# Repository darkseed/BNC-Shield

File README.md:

Documentation:

http://www.practicalmaker.com/node/77

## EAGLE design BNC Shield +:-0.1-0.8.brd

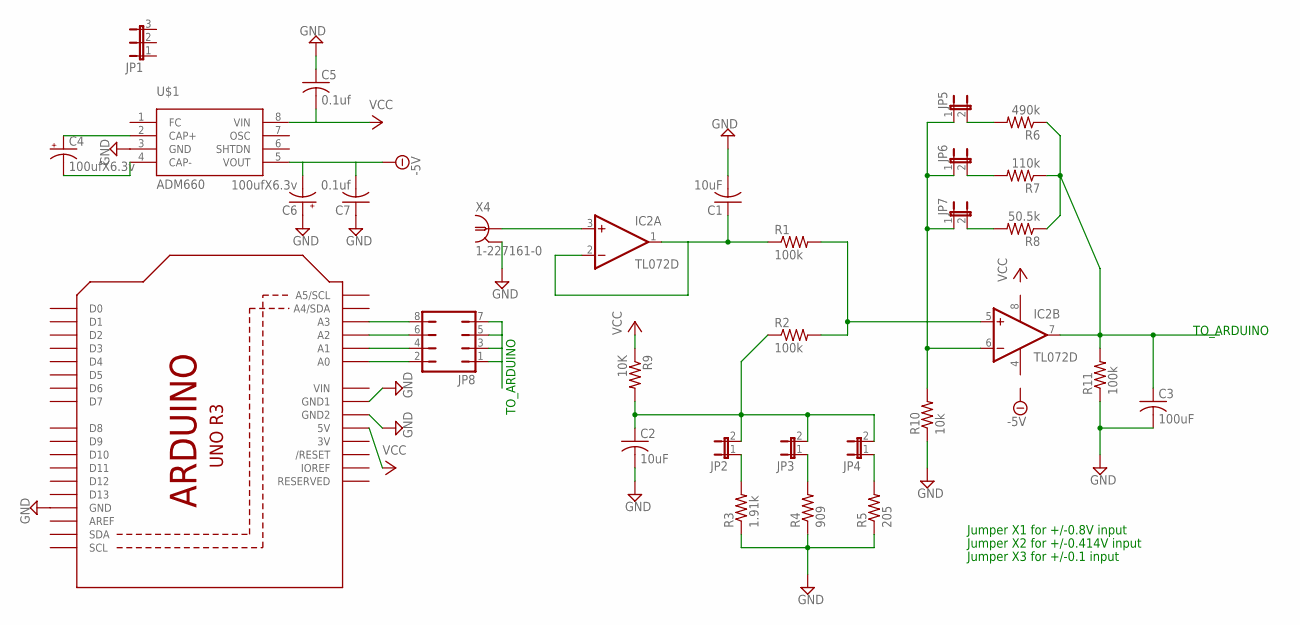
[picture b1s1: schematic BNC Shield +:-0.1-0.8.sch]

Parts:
C1, C2: 10uF; C0603
C3: 100uF; C0603
C4, C6: 100ufX6.3v; 153CLV-0605
C5, C7: 0.1uf; C0603
IC2: TL072D; SO08
JP1: JP2E; JP2
JP2, JP3, JP4, JP5, JP6, JP7: JP1E; JP1
JP8: JP4Q
R1, R2, R11: 100k; R0603
R3: 1.91k; R0603
R4: 909; R0603
R5: 205; R0603
R6: 490k; R0603
R7: 110k; R0603
R8: 50.5k; R0603
R9: 10K; R0603
R10: 10k; R0603
U1: ARDUINOR3-DIMENSION; ARDUINOR3
U$1: ADM660; SO8
X4: 1-227161-0; AMP_227161

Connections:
3V: U1.3V
-5V: C6.-, C7.2, U$1.5 (VOUT)
GND: C1.2, C2.2, C3.2, C5.1, C6.+, C7.1, R3.1, R4.1, R5.1, R10.1, R11.1, U1.GND, U1.GND1, U1.GND2, U$1.3 (GND), X4.2 (GND)
unnamed: C1.1, IC2.1 (OUT), IC2.2 (-IN), R1.1
unnamed: JP2.1, R3.2
unnamed: JP3.1, R4.2
unnamed: JP4.1, R5.2
unnamed: IC2.5 (+IN), R1.2, R2.2
unnamed: C2.1, JP2.2, JP3.2, JP4.2, R2.1, R9.2
unnamed: JP5.2, R6.2
unnamed: JP6.2, R7.2
unnamed: JP7.2, R8.2
unnamed: C4.+, U$1.2 (CAP+)
unnamed: IC2.6 (-IN), JP5.1, JP6.1, JP7.1, R10.2
unnamed: IC2.3 (+IN), X4.1
unnamed: JP8.2, U1.A0
unnamed: JP8.4, U1.A1
unnamed: JP8.6, U1.A2
unnamed: JP8.8, U1.A3
unnamed: C4.-, U$1.4 (CAP-)
TO_ARDUINO: C3.1, IC2.7 (OUT), JP8.1, JP8.3, JP8.5, JP8.7, R6.1, R7.1, R8.1, R11.2
V+: IC2.8 (V+)
V-: IC2.4 (V-)
VCC: C5.2, R9.1, U1.5V, U$1.8 (VIN)
VIN: U1.VIN

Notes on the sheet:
Jumper X1 for +/-0.8V input
Jumper X2 for +/-0.414V input
Jumper X3 for +/-0.1 input
TO_ARDUINO

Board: 2 copper layers, 30 parts (1 on the bottom side), 21 nets, no tracks yet.

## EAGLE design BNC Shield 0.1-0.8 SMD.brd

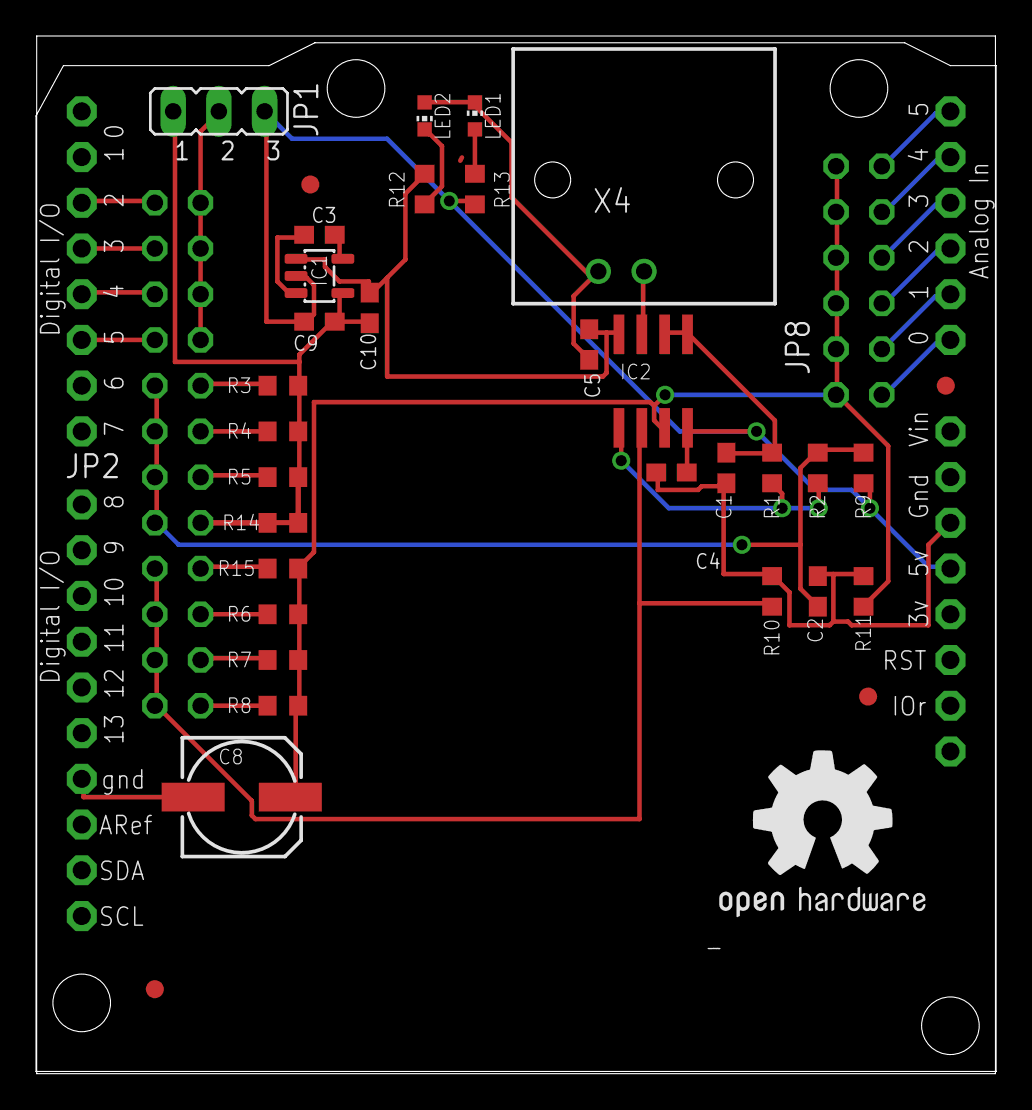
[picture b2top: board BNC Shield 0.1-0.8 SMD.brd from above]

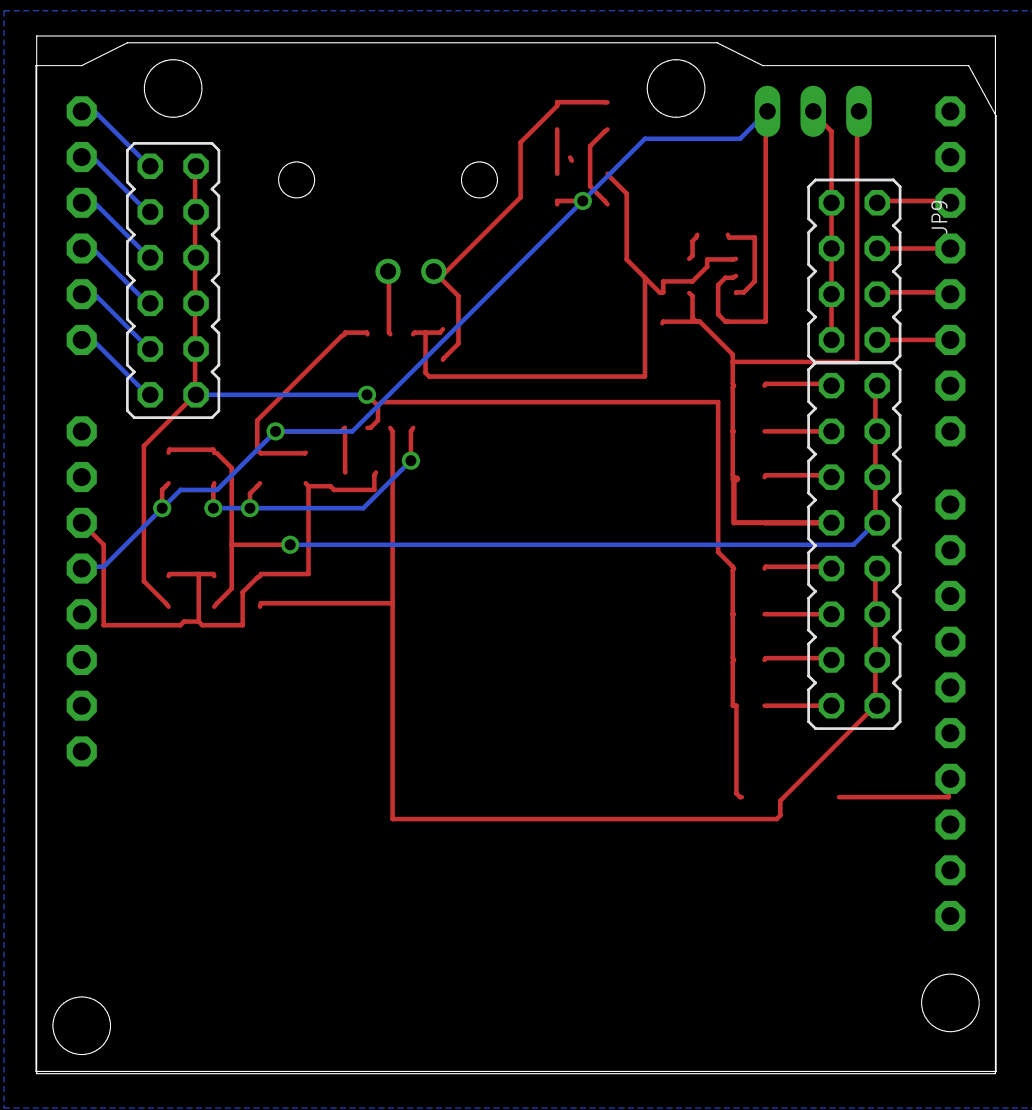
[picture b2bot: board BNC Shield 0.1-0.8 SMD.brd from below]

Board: 2 copper layers, 53.3 x 57.6 mm, 38 parts (3 on the bottom side), 32 nets.

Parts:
C1, C2: 10uF; C0603
C3, C9, C10: 1u; C603
C4, C5: 0.1uf; C603
C8: 100ufX6.3v; 153CLV-0605
IC1: TPS60400DBV; SOT23-DBV
IC2: TL072D; SO08
JP1: JP2
JP2: JP8Q
JP8: JP6Q
JP9: JP4Q
LED1, LED2: CHIP-LED0603
R1, R2, R11: 100k; R0603
R3: 1.91k; R0603
R4: 909; R0603
R5: 400; R0603
R6: 110k; R0603
R7: 240k; R0603
R8: 490k; R0603
R9: 10K; R0603
R10: 10k; R0603
R12, R13: 150; R0603
R14: 205; R0603
R15: 51k; R0603
U1: ARDUINOR3-DIMENSION; ARDUINOR3
U$1: OSHW1
U$2, U$3, U$4, U$5: FIDUCIAL; FIDUCIAL_1MM
X4: 1-227161-0; AMP_227161

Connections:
-5V: C5.1, C10.2, IC1.1, IC2.4, R12.2
GND: C1.2, C2.2, C4.2, C5.2, C8.-, C9.2, C10.1, IC1.4, JP1.1, LED1.C, LED2.A, R3.1, R4.1, R5.1, R10.1, R11.1, R14.1, U1.GND, U1.GND1, U1.GND2, X4.2
unnamed: C1.1, IC2.1, IC2.2, R1.1
unnamed: JP2.1, R3.2
unnamed: JP2.3, R4.2
unnamed: JP2.5, R5.2
unnamed: IC2.5, R1.2, R2.2
unnamed: C2.1, JP2.2, JP2.4, JP2.6, JP2.8, R2.1, R9.2
unnamed: JP2.11, R6.2
unnamed: JP2.13, R7.2
unnamed: JP2.15, R8.2
unnamed: JP9.1, U1.D5
unnamed: IC2.6, JP2.10, JP2.12, JP2.14, JP2.16, R10.2
unnamed: IC2.3, X4.1
unnamed: JP8.2, U1.A0
unnamed: JP8.4, U1.A1
unnamed: JP8.6, U1.A2
unnamed: JP8.8, U1.A3
unnamed: JP9.3, U1.D4
unnamed: LED2.C, R12.1
unnamed: LED1.A, R13.2
unnamed: JP8.10, U1.A4
unnamed: C3.1, IC1.3
unnamed: C3.2, IC1.5
unnamed: JP9.5, U1.D3
unnamed: JP9.7, U1.D2
unnamed: JP8.12, U1.A5
unnamed: JP2.7, R14.2
unnamed: JP2.9, R15.2
ONEWIRE_DATA: JP1.2, JP9.2, JP9.4, JP9.6, JP9.8
TO_ARDUINO: C8.+, IC2.7, JP8.1, JP8.3, JP8.5, JP8.7, JP8.9, JP8.11, R6.1, R7.1, R8.1, R11.2, R15.1
VCC: C4.1, C9.1, IC1.2, IC2.8, JP1.3, R9.1, R13.1, U1.5V

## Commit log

2013-07-24 push
2014-01-25 push to github
2014-01-25 add readme
